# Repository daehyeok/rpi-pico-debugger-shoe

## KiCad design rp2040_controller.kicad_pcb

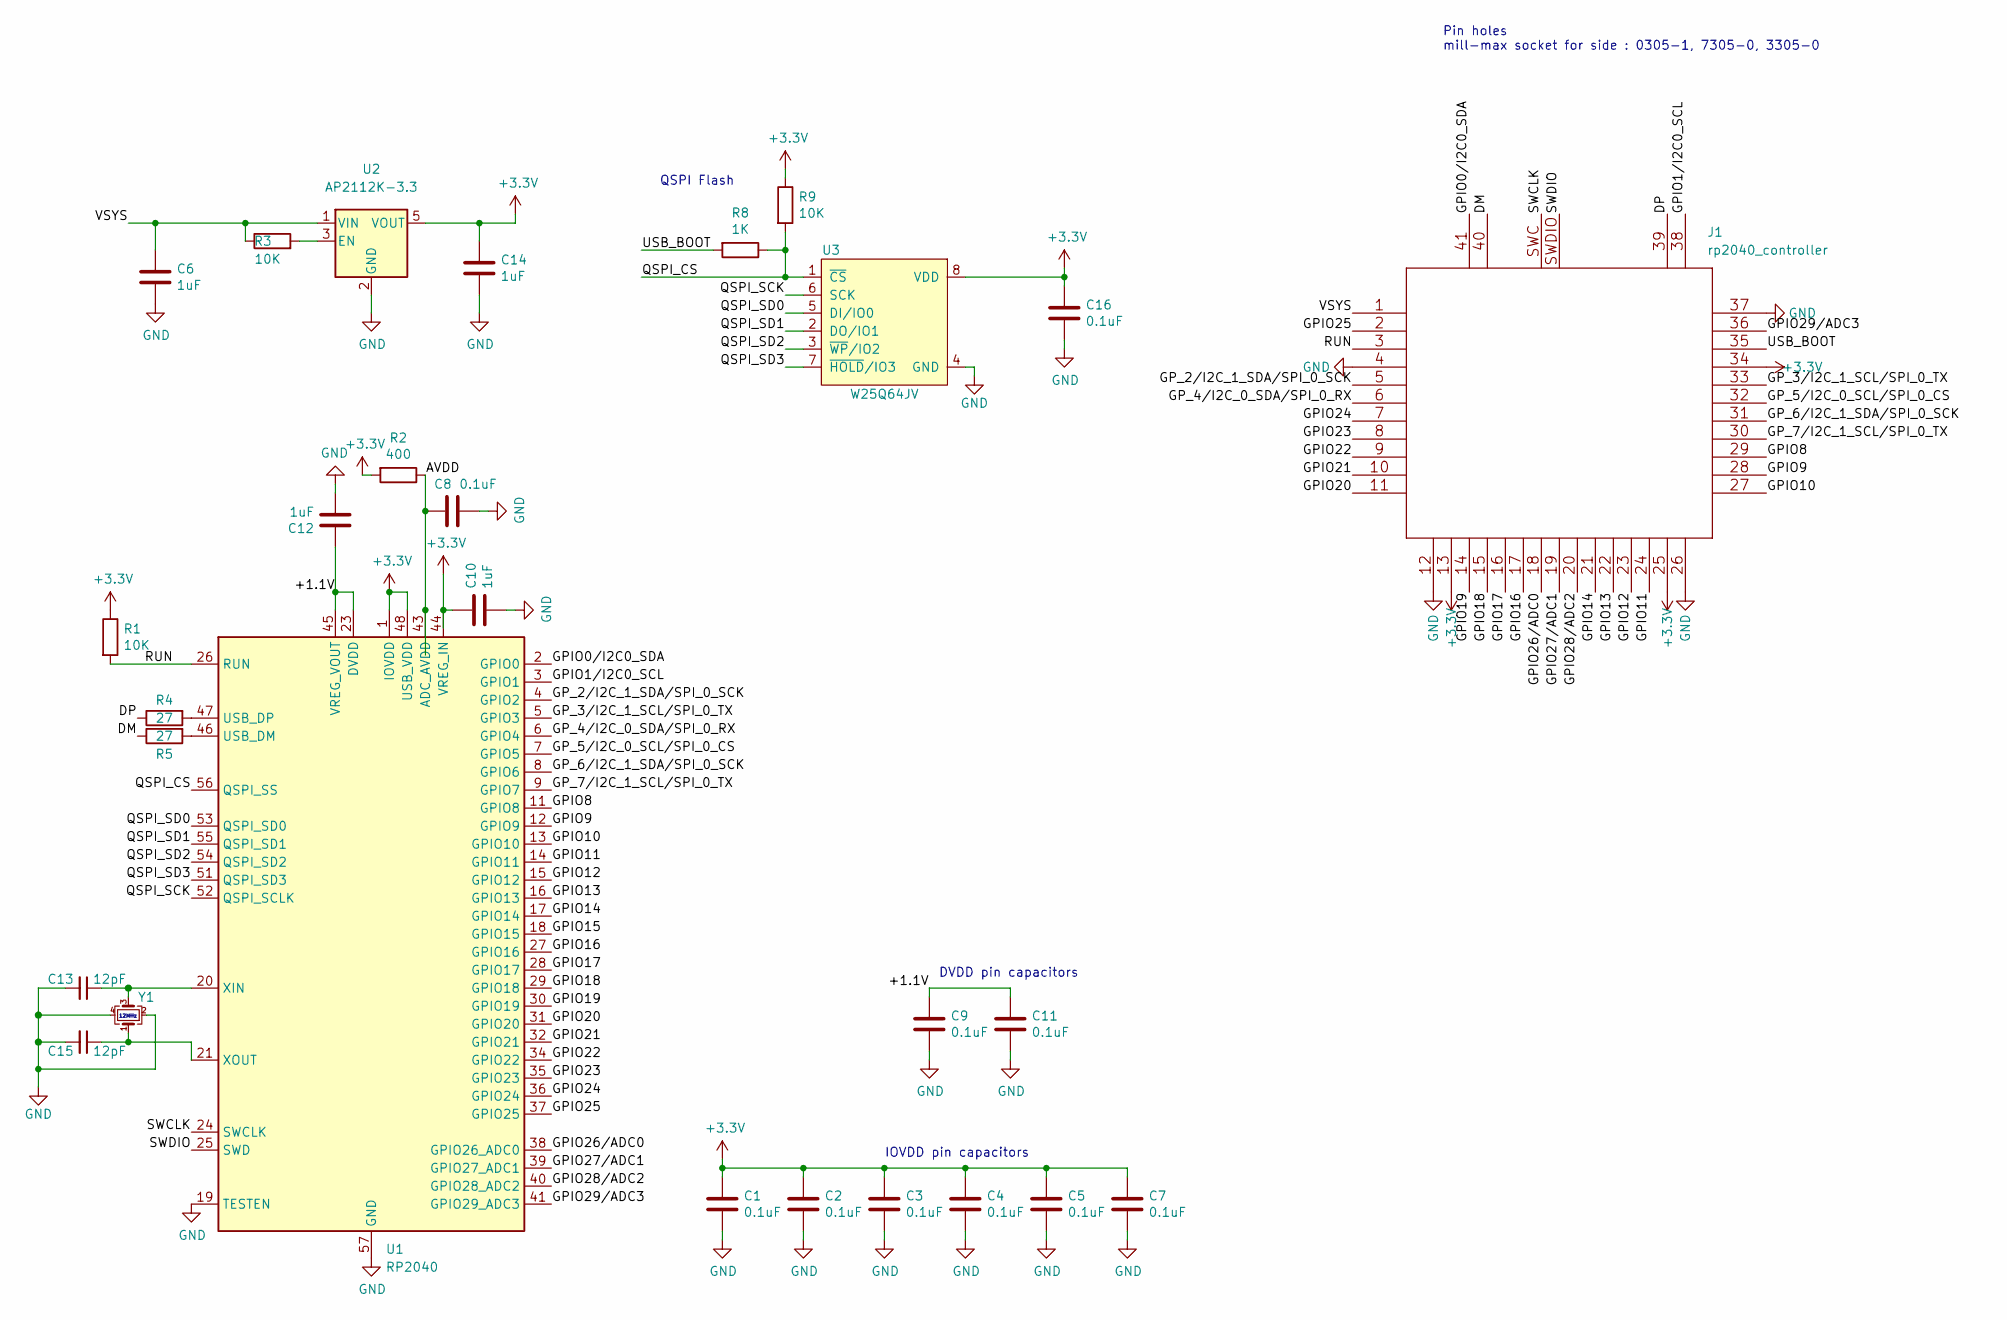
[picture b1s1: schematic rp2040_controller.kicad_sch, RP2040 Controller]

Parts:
C1, C2, C3, C4, C5, C7, C8, C9, C11, C16: 0.1uF; C_0603_1608Metric_Pad1.08x0.95mm; Digi-Key_PN 311-1344-1-ND
C6, C10, C12, C14: 1uF; C_0603_1608Metric_Pad1.08x0.95mm; Digi-Key_PN 1276-6524-1-ND
C13, C15: 12pF; C_0603_1608Metric_Pad1.08x0.95mm
J1: rp2040_controller
R1, R3, R9: 10K; R_0603_1608Metric_Pad0.98x0.95mm_HandSolder; Digi-Key_PN 311-10KGRCT-ND
R2: 400; R_0603_1608Metric_Pad0.98x0.95mm_HandSolder; Digi-Key_PN 311-27.0HRCT-ND
R4, R5: 27; R_0603_1608Metric_Pad0.98x0.95mm_HandSolder; Digi-Key_PN 311-27.0HRCT-ND
R8: 1K; R_0603_1608Metric_Pad0.98x0.95mm_HandSolder; Digi-Key_PN 311-1.00KHRCT-ND
U1: RP2040; QFN-56-1EP_7x7mm_P0.4mm_EP3.2x3.2mm
U2: AP2112K-3.3; SOT-23-5
U3: W25Q64JV; WSON-8-1EP_6x5mm_P1.27mm_EP3.4x4mm
Y1: XYDBPCNANF-12MHZ; Crystal_SMD_2520-4Pin_2.5x2.0mm; LCSC C521567

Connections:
+3V3: C1.1, C2.1, C3.1, C4.1, C5.1, C7.1, C10.1, C14.1, C16.1, J1.13 (GPIO10), J1.25 (SWDIO), J1.34 (GPIO22), R1.1, R2.2, R9.1, U1.1 (IOVDD), U1.10 (IOVDD), U1.22 (IOVDD), U1.33 (IOVDD), U1.42 (IOVDD), U1.44 (VREG_IN), U1.48 (USB_VDD), U1.49 (IOVDD), U2.5 (VOUT), U3.8 (VDD)
/+1.1V: C9.1, C11.1, C12.1, U1.23 (DVDD), U1.45 (VREG_VOUT), U1.50 (DVDD)
/AVDD: C8.1, R2.1, U1.43 (ADC_AVDD)
/DM: J1.40 (GPIO28/ADC2), R5.1
/DP: J1.39 (GPIO27/ADC1), R4.1
/GPIO0/I2C0_SDA: J1.41 (GPIO29/ADC3), U1.2 (GPIO0)
/GPIO1/I2C0_SCL: J1.38 (GPIO26/ADC0), U1.3 (GPIO1)
/GPIO8: J1.29 (GPIO18), U1.11 (GPIO8)
/GPIO9: J1.28 (GPIO17), U1.12 (GPIO9)
/GPIO10: J1.27 (GPIO16), U1.13 (GPIO10)
/GPIO11: J1.24 (SWCLK), U1.14 (GPIO11)
/GPIO12: J1.23 (DVDD), U1.15 (GPIO12)
/GPIO13: J1.22 (IOVDD), U1.16 (GPIO13)
/GPIO14: J1.21 (XOUT), U1.17 (GPIO14)
/GPIO15: U1.18 (GPIO15)
/GPIO16: J1.17 (GPIO14), U1.27 (GPIO16)
/GPIO17: J1.16 (GPIO13), U1.28 (GPIO17)
/GPIO18: J1.15 (GPIO12), U1.29 (GPIO18)
/GPIO19: J1.14 (GPIO11), U1.30 (GPIO19)
/GPIO20: J1.11 (GPIO8), U1.31 (GPIO20)
/GPIO21: J1.10 (IOVDD), U1.32 (GPIO21)
/GPIO22: J1.9 (GPIO7), U1.34 (GPIO22)
/GPIO23: J1.8 (GPIO6), U1.35 (GPIO23)
/GPIO24: J1.7 (GPIO5), U1.36 (GPIO24)
/GPIO25: J1.2 (GPIO0), U1.37 (GPIO25)
/GPIO26/ADC0: J1.18 (GPIO15), U1.38 (GPIO26_ADC0)
/GPIO27/ADC1: J1.19 (TESTEN), U1.39 (GPIO27_ADC1)
/GPIO28/ADC2: J1.20 (XIN), U1.40 (GPIO28_ADC2)
/GPIO29/ADC3: J1.36 (GPIO24), U1.41 (GPIO29_ADC3)
/GP_2/I2C_1_SDA/SPI_0_SCK: J1.5 (GPIO3), U1.4 (GPIO2)
/GP_3/I2C_1_SCL/SPI_0_TX: J1.33 (IOVDD), U1.5 (GPIO3)
/GP_4/I2C_0_SDA/SPI_0_RX: J1.6 (GPIO4), U1.6 (GPIO4)
/GP_5/I2C_0_SCL/SPI_0_CS: J1.32 (GPIO21), U1.7 (GPIO5)
/GP_6/I2C_1_SDA/SPI_0_SCK: J1.31 (GPIO20), U1.8 (GPIO6)
/GP_7/I2C_1_SCL/SPI_0_TX: J1.30 (GPIO19), U1.9 (GPIO7)
/QSPI_CS: R8.1, R9.2, U1.56 (QSPI_SS), U3.1 (~CS)
/QSPI_SCK: U1.52 (QSPI_SCLK), U3.6 (SCK)
/QSPI_SD0: U1.53 (QSPI_SD0), U3.5 (DI/IO0)
/QSPI_SD1: U1.55 (QSPI_SD1), U3.2 (DO/IO1)
/QSPI_SD2: U1.54 (QSPI_SD2), U3.3 (~WP/IO2)
/QSPI_SD3: U1.51 (QSPI_SD3), U3.7 (~HOLD/IO3)
/RUN: J1.3 (GPIO1), R1.2, U1.26 (RUN)
/SWCLK: J1.SWC, U1.24 (SWCLK)
/SWDIO: J1.SWDIO, U1.25 (SWD)
/USB_BOOT: J1.35 (GPIO23), R8.2
/VSYS: C6.1, J1.1 (IOVDD), R3.1, U2.1 (VIN)
GND: C1.2, C2.2, C3.2, C4.2, C5.2, C6.2, C7.2, C8.2, C9.2, C10.2, C11.2, C12.2, C13.2, C14.2, C15.2, C16.2, J1.4 (GPIO2), J1.12 (GPIO9), J1.26 (RUN), J1.37 (GPIO25), U1.19 (TESTEN), U1.57 (GND), U2.2 (GND), U3.4 (GND), U3.9 (GND), Y1.2, Y1.4
unnamed: R5.2, U1.46 (USB_DM)
unnamed: R4.2, U1.47 (USB_DP)
unnamed: C13.1, U1.20 (XIN), Y1.3
unnamed: C15.1, U1.21 (XOUT), Y1.1
unnamed: R3.2, U2.3 (EN)

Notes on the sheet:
Pin holes mill-max socket for side : 0305-1, 7305-0, 3305-0
DVDD pin capacitors
12MHz
QSPI Flash
IOVDD pin capacitors

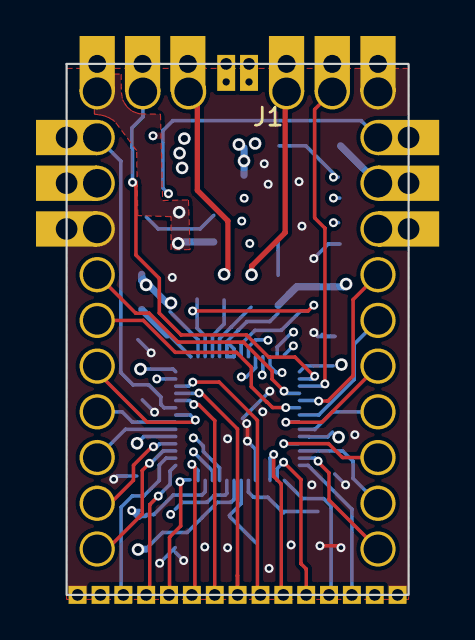
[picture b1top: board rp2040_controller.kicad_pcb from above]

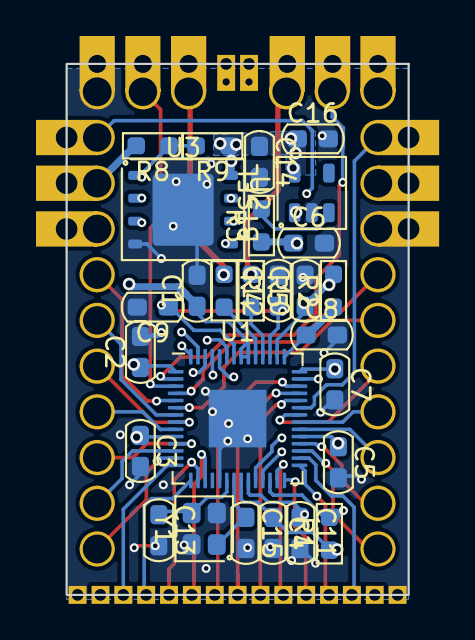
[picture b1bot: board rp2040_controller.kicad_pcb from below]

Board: 4 copper layers, 19.0 x 29.5 mm, 28 parts (27 on the bottom side), 51 nets.

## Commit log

2023-04-03 Fork&init project
2023-04-04 init
2023-04-06 temp
2023-04-06 v0.1
2023-04-07 v0.2
2023-04-07 v0.3
2023-04-07 top&bottom connect
2023-04-07 Kicad 7

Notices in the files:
rp2040_controller.kicad_pcb:
https://creativecommons.org/licenses/by/4.0
License: CC BY 4.0
rp2040_controller.kicad_sch:
License: CC BY 4.0 https://creativecommons.org/licenses/by/4.0
